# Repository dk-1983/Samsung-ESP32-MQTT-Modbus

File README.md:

# Samsung-ESP32-MQTT-Modbus — 1.0.2

[Русский](README_RU.md)

**[Download stable v1.0.2](https://github.com/dk-1983/Samsung-ESP32-MQTT-Modbus/releases/tag/v1.0.2)** — ready-made OTA binary for already provisioned ESP32-S3 N16R8 controllers. Not a first-install image for a blank board.

**Keep Samsung's factory features and add 4VRS control.**

Samsung-ESP32-MQTT-Modbus is an ESP32-S3 expansion controller with a transparent
inline UART bridge between the AC motherboard and its original display/Wi-Fi board.
The architecture is designed to preserve the full factory functionality: the
original boards keep communicating, while the IR remote, display and Samsung
SmartThings coexist with the additional 4VRS interfaces.

Our 4VRS polling and command dispatcher runs on the ESP32. It tracks factory
transactions, selects an idle window for each own request and coordinates access
from the web controls, MQTT and Modbus to the shared UART bus. A command is confirmed
only by reading the actual AC state. Unknown factory packets are forwarded unchanged,
so forwarding is not limited to the commands implemented by our firmware.

Additional interfaces:

- **Wi-Fi:** local network connectivity and OTA firmware updates.
- **HTTP Remote:** a local web remote and HTTP API for control over the network.
- **MQTT / Home Assistant Discovery:** automatic device and entity discovery. No custom Samsung/4VRS integration, HACS package or manual entity configuration is required; use the standard MQTT integration with your broker.
- **Modbus RTU / TCP:** RS485 and network automation integration.

Local 4VRS interfaces do not require Samsung's cloud. Factory SmartThings retains
its own connection through the original Wi-Fi module. Display, IR remote and
SmartThings control have been checked with the bridge on AR24BSFCMWKNER;
exhaustive validation of every factory function is still pending.

Repository: [dk-1983/Samsung-ESP32-MQTT-Modbus](https://github.com/dk-1983/Samsung-ESP32-MQTT-Modbus).
See [bridge wiring and limitations](docs/UART_BRIDGE.md).

Home Assistant is optional: connect the controller to your own MQTT broker and automation server. See [topics, commands, states and the complete Discovery-based inventory](docs/HOME_ASSISTANT.md#own-mqtt-broker-without-home-assistant).

[Complete Modbus register list with Samsung / 4VRS separation](docs/MODBUS.md): the factory indoor-unit range ends at **2449**, and our extensions begin at **2450**.

[Electrical schematic, wiring and PCB component libraries](hardware/README.md).

## Home Assistant via Modbus Devices

**[Modbus Devices](https://github.com/dk-1983/Modbus_Devices#4vrs) includes a dedicated profile for this controller: manufacturer `4VRS`, model `Samsung-ESP32-Modbus`.**

Connect through Modbus TCP over Wi-Fi or Modbus RTU over RS485 to get climate
control, the full fan/swing/preset controls, confirmed writes, and link and command
diagnostics in Home Assistant. The profile uses our extended register map;
you do not need to enter each register manually. MQTT is not required for this option.

1. Install [Modbus Devices](https://github.com/dk-1983/Modbus_Devices#installation) in Home Assistant.
2. Open `/modbus` on the controller and enable TCP or RTU.
3. Add the device using **4VRS → Samsung-ESP32-Modbus** and your connection settings.
   For direct TCP, use the controller IP, port **502** and configured Unit ID (default **1**).
   For RTU, match the controller's serial settings (default **9600 8E1**).

Select the **4VRS** profile for this device; the Samsung **MIM-B19N(T)** profile
is for the factory adapter. For MQTT-based setup, use Home Assistant's standard
MQTT integration with Discovery as described above.

## Electrical schematic

Motherboard UART: **RX18 / TX17**. Original display/Wi-Fi board: **RX15 / TX16**.
Modbus RS485: **RX8 / TX9 / DE21**. Numbers are ESP32 GPIOs, not module pad numbers.
Both Samsung boards retain their +5 V and common ground connections.

[Open full-resolution schematic](hardware/drawings/preview-1.png) · [Vector PDF](hardware/drawings/Samsung_transparency_bridge_revA-review.pdf) · [PCB component libraries](hardware/README.md)

## Controls and connections

The portal on port 80 links to controls, MQTT, Modbus and GitHub updates.
The Control link opens `/control`; advanced ESPHome controls remain on port 8080.
Both use `admin` and the same password stored on the device.

The main web interface on port 80 supports English and Russian. English is the
default; use the language selector to switch. Your browser remembers the selection.
This selector does not change the advanced ESPHome interface on port 8080.

- Independent persistent checkboxes for MQTT, Modbus RTU and Modbus TCP; all default off.
- Browser-configured MQTT broker/port/credentials/topic prefix and Home Assistant discovery.
- Browser-configured Modbus unit and RS485 baud rate; RTU defaults to 9600 8E1, TCP port 502.
- GitHub automatic-install checkbox, manual check/install, progress, signed manifest,
  board profile, SHA256 validation and rollback.
- Local ESPHome OTA remains available and is coordinated with the GitHub worker.

[Management and releases](docs/MANAGEMENT.md) · [Full device register map](docs/MODBUS.md)
· [Home Assistant MQTT Discovery](docs/HOME_ASSISTANT.md)
· [Modbus register reference (Russian)](docs/MODBUS_REGISTERS_RU.md)
· [UART function reference](docs/FUNCTIONS_RU.md)

UART TX/RX GPIO17/18 uses 9600 8N1. RS485 TX/RX/DE uses 9/8/21.
The AC uses D0 UART, not native Modbus; ESP32 implements the external register map.
Core addresses follow MIM-B19N/B19NT; custom functions begin at 2450.

UART is enabled on every boot and can be disabled in the control page.
Saving MQTT settings reboots the controller after two seconds to apply credentials.
Feedback is never optimistic: acknowledgement is not proof of the requested AC state.

## Hardware compatibility, first installation and updates

**Inline bridge support starts with firmware 0.5.0. Versions 0.4.x use the earlier
non-bridge configuration; 0.5.0 and later target the bridge wiring shown here.**
From the ESP32 side, the AC motherboard uses RX GPIO18 / TX GPIO17, the original
Wi-Fi/display board uses RX GPIO15 / TX GPIO16, and Modbus RS485 uses
RX GPIO8 / TX GPIO9 / DE GPIO21.
Module pads 8/9 are GPIO15/16 (the bridge), not GPIO8/9 (Modbus).

Boards wired for the pre-0.5.0 non-bridge configuration are a different hardware
configuration.
Do not install the current OTA on them solely because their firmware version is
older. Check the wiring against the current schematic first; an OTA update does
not add the missing bridge connection or change the PCB routing.

- **Configured controller with the current bridge wiring:** update through
  `/updates`. A working 1.0.0 or 1.0.1 installation on this hardware can update
  directly; no intermediate version is required. Preserve NVS when updating.
- **New controller with the current bridge wiring:** build the current stable
  source with `./Build.ps1`, personal `secrets.yaml` and `public_release: "false"`
  (the default). Use `firmware.factory.bin` for initial USB/serial installation.
  First boot saves the web, local OTA and Samsung-Setup passwords in NVS.
  Connect to Samsung-Setup with your setup password and configure Wi-Fi at
  `http://192.168.4.1:8080/`. Subsequent updates can use public OTA releases.

The public `*-ota.bin` requires existing device credentials in NVS; it is not a
first-install image for a blank board. A ready-made public provisioning image is
not provided yet. Installing an old firmware version first is not required.
Hardware compatibility and initial credential provisioning are separate requirements.

## Build and validation

Run `./Build.ps1` to install pinned dependencies, run host tests and build, without
flashing. Local configuration is in `secrets.yaml`; neither it nor locally built
private binaries belong in a public release. OTA/factory binaries are under
`work/build/.pioenvs/samsung-s3`. On the first local build boot, credentials are saved
to NVS and survive subsequent public OTA updates.

The separate GitHub workflow prepares a clean public **OTA-only** artifact for
controllers with the current bridge wiring and provisioned credentials. Signing/publishing is a separate step.
See [release preparation](docs/MANAGEMENT.md#release).

Power, fan Low/Medium/High/Turbo and both swing axes were tested on the target AC
in earlier firmware. Persistent web settings, Modbus TCP and GitHub OTA have
been checked on a device, including credential/settings retention and boot confirmation.
Authenticated MQTT connectivity is verified. Physical RS485 and forced rollback still need testing.
Experimental legacy controls require per-function verification on this model.

[Protocol](docs/PROTOCOL.md) · [Attribution](THIRD_PARTY.md)

The `/about` page shows firmware, memory, connections and UART freshness.
Restart requires confirmation and preserves settings. It is rejected during OTA
or while an AC command is pending.

`/settings` independently changes web, local OTA and Samsung-Setup passwords.
Blank fields preserve current credentials; new values require confirmation.
Changes are stored in NVS and applied on restart. Forgotten-password recovery
is not implemented yet.

`/wifi` shows network, IP, MAC, signal and channel. `/wifi/reset` confirms a
Wi-Fi-only reset; reprovision through Samsung-Setup at `192.168.4.1:8080`.
Other settings are preserved.

[Overview, web controls and MQTT power commands (Russian)](docs/CONTROL_RU.md).

HVAC commands require fresh control permission and feedback. Requested power is
never restored automatically after a restart.

In inline mode the factory board owns startup and notification ACKs. Own writes
require fresh permission and feedback, use an idle transaction window and are
confirmed by own readback, never by ACK alone. No automatic write retries.
Main RX18/TX17, factory RX15/TX16, RS485 RX8/TX9/DE21. All three hardware
UARTs are used; serial logging is disabled, web logging remains available.
Disabling UART transmission also stops factory forwarding.

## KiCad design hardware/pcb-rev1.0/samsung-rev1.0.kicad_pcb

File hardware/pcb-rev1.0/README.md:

# Samsung UART bridge — PCB rev1.0

[Русский](README_RU.md)

30 × 48 mm (48 × 30 when rotated), two copper layers, 1.0 mm thickness in KiCad. Components on both sides, no mounting holes. Based on the Haier pcb-v1.1 circuit; the Haier project was not modified.

Files: samsung-rev1.0.kicad_pcb; review/samsung-both-sides.png (review only); circuit.json, connections.csv and BOM.csv; drc.json; review/pin-check.json; reproducible scripts in sources/.

KiCad DRC: 0 violations and 0 unconnected items. All 82 assigned logical pads match circuit.json. 25 U1/U2/U3 assignments independently match the Samsung schematic. This PCB has not been tested on hardware. Gerber and drill files are included in production/, together with an archive and a checksum manifest.

## Solder pads

MAIN and DISPLAY TX/RX labels refer to the external Samsung board, not the ESP.

- TP9–TP12 MAIN, left to right viewed from top: +5V, GND, motherboard TX through divider to GPIO18, motherboard RX from GPIO17.
- TP13–TP16 DISPLAY: +5V, GND, display TX through divider to GPIO15, display RX from GPIO16.
- TP7/TP8: RS485 A/B.
- TP1/TP2/TP3: programming TX0 GPIO43 / RX0 GPIO44 / GND.
- TP4/TP5/TP6 on bottom: EN / BOOT GPIO0 / 3V3 voltage monitor.

UART solder pads are 2 mm in diameter. No UART connectors. All power and grounds are common. Preserve factory Samsung connections outside the UART bridge.

RS485 uses GPIO8 RX, GPIO9 TX, GPIO21 DE and /RE. R6 10k pulls direction down. R7 120 ohm and solder jumper JP1 enable termination. All three RX inputs use 10k/20k dividers; ESP TX outputs are direct 3.3V.

## Assembly and references

PCB component numbering follows the Haier carrier and differs from the older Samsung revA PDF. Use this PCB's BOM.csv and connections.csv. Old Samsung resistor → PCB mapping: R1→R1, R2→R9, R3→R8, R4→R2, R5→R3, R6→R5, R7→R4, R8→R6. PCB R7 adds termination.

The Haier power circuit is retained: LM1117-3.3 SOT-223, 220uF and 100uF case-C capacitors and ceramic decoupling. This expands the old Samsung revA drawing, whose 47uF C2 package was unresolved. The regulator TAB and its thermal planes are +3V3, not GND. ESP ground planes and thermal vias remain separate. Both copper layers are clear beneath the antenna.

This PCB requires factory plated holes, unlike the homemade kitchen-hood PCB. Verify mechanical fit and the BOM against available components before ordering. No firmware, device or release changes were performed.

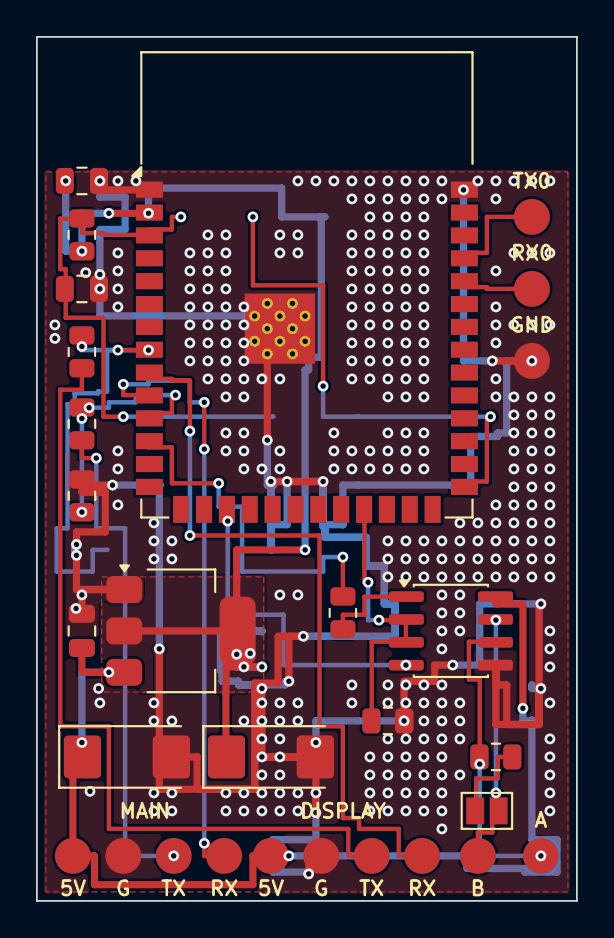
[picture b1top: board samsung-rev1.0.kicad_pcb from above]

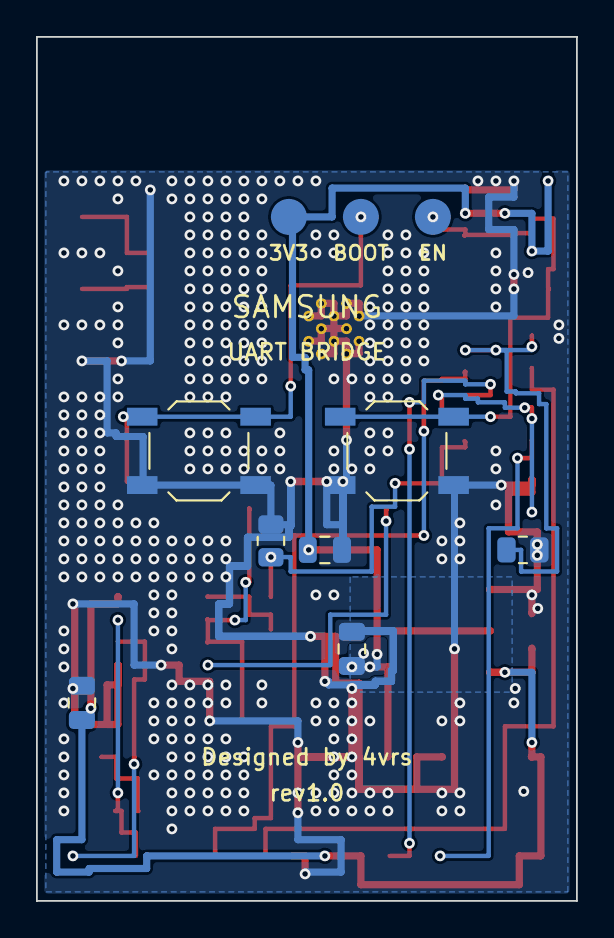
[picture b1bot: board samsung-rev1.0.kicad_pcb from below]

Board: 2 copper layers, 30.0 x 48.0 mm, 39 parts (10 on the bottom side), 20 nets.

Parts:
C1: 220u 10V; CP_EIA-6032-28_Kemet-C
C2, C4, C5, C6: 100n 50V; C_0805_2012Metric
C3: 100u 10V; CP_EIA-6032-28_Kemet-C
C7: 1u 16V; C_0805_2012Metric
C8: 10u 10V; C_0805_2012Metric
JP1: TERM ENABLE; SolderJumper-2_P1.3mm_Open_Pad1.0x1.5mm
R1, R2, R4, R6, R8: 10k; R_0805_2012Metric
R3, R5, R9: 20k; R_0805_2012Metric
R7: 120; R_0805_2012Metric
SB1: SB1; SW_SPST_TL3342
SB2: SB2; SW_SPST_TL3342
TP1: UART0_TX; TestPoint_Pad_D2.0mm
TP2: UART0_RX; TestPoint_Pad_D2.0mm
TP3, TP10, TP14: GND; TestPoint_Pad_D2.0mm
TP4: EN; TestPoint_Pad_D2.0mm
TP5: BOOT; TestPoint_Pad_D2.0mm
TP6: +3V3; TestPoint_Pad_D2.0mm
TP7: A; TestPoint_Pad_D2.0mm
TP8: B; TestPoint_Pad_D2.0mm
TP9, TP13: +5V; TestPoint_Pad_D2.0mm
TP11: MAIN_TX_5V; TestPoint_Pad_D2.0mm
TP12: H_TX; TestPoint_Pad_D2.0mm
TP15: FACTORY_TX; TestPoint_Pad_D2.0mm
TP16: F_TX; TestPoint_Pad_D2.0mm
U1: ESP32-S3-WROOM-1-N16R8; ESP32-S3-WROOM-1
U2: LM1117-3.3; SOT-223-3_TabPin2
U3: MAX485; SOIC-8_3.9x4.9mm_P1.27mm

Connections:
+3V3: C3.1, C4.1, C5.1, C8.1, R1.1, TP6.1, U1.2, U2.2
+5V: C1.1, C2.1, C6.1, TP9.1, TP13.1, U2.3, U3.8
A: R7.1, TP7.1, U3.6
B: JP1.2, TP8.1, U3.7
BOOT: SB1.1, TP5.1, U1.27
DIR: R6.1, U1.23, U3.2, U3.3
EN: C7.1, R1.2, SB2.1, TP4.1, U1.3
FACTORY_TX: R8.1, TP15.1
F_RX: R8.2, R9.1, U1.8
F_TX: TP16.1, U1.9
GND: C1.2, C2.2, C3.2, C4.2, C5.2, C6.2, C7.2, C8.2, R3.2, R5.2, R6.2, R9.2, SB1.2, SB2.2, TP3.1, TP10.1, TP14.1, U1.1, U1.40, U1.41, U2.1, U3.5
H_RX: R2.2, R3.1, U1.11
H_TX: TP12.1, U1.10
MAIN_TX_5V: R2.1, TP11.1
MB_RX: R4.2, R5.1, U1.12
MB_TX: U1.17, U3.4
RO_5V: R4.1, U3.1
TERM: JP1.1, R7.2
UART0_RX: TP2.1, U1.36
UART0_TX: TP1.1, U1.37

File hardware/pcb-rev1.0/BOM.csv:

Reference,Value,Footprint,MPN
U1,ESP32-S3-WROOM-1-N16R8,RF_Module:ESP32-S3-WROOM-1,ESP32-S3-WROOM-1-N16R8
U2,LM1117-3.3,Package_TO_SOT_SMD:SOT-223-3_TabPin2,LM1117MP-3.3
U3,MAX485,Package_SO:SOIC-8_3.9x4.9mm_P1.27mm,MAX485ESA+
R1,10k,Resistor_SMD:R_0805_2012Metric,
R2,10k,Resistor_SMD:R_0805_2012Metric,
R3,20k,Resistor_SMD:R_0805_2012Metric,
R4,10k,Resistor_SMD:R_0805_2012Metric,
R5,20k,Resistor_SMD:R_0805_2012Metric,
R8,10k,Resistor_SMD:R_0805_2012Metric,
R9,20k,Resistor_SMD:R_0805_2012Metric,
R6,10k,Resistor_SMD:R_0805_2012Metric,
R7,120,Resistor_SMD:R_0805_2012Metric,
C1,220u 10V,Capacitor_Tantalum_SMD:CP_EIA-6032-28_Kemet-C,TAJC227M010RNJ
C3,100u 10V,Capacitor_Tantalum_SMD:CP_EIA-6032-28_Kemet-C,TAJC107M010RNJ
C2,100n 50V,Capacitor_SMD:C_0805_2012Metric,
C4,100n 50V,Capacitor_SMD:C_0805_2012Metric,
C5,100n 50V,Capacitor_SMD:C_0805_2012Metric,
C6,100n 50V,Capacitor_SMD:C_0805_2012Metric,
C7,1u 16V,Capacitor_SMD:C_0805_2012Metric,
C8,10u 10V,Capacitor_SMD:C_0805_2012Metric,
SB1,SB1,Button_Switch_SMD:SW_SPST_TL3342,
SB2,SB2,Button_Switch_SMD:SW_SPST_TL3342,
JP1,TERM ENABLE,Jumper:SolderJumper-2_P1.3mm_Open_Pad1.0x1.5mm,
TP1,UART0_TX,TestPoint:TestPoint_Pad_D2.0mm,
TP2,UART0_RX,TestPoint:TestPoint_Pad_D2.0mm,
TP3,GND,TestPoint:TestPoint_Pad_D2.0mm,
TP4,EN,TestPoint:TestPoint_Pad_D2.0mm,
TP5,BOOT,TestPoint:TestPoint_Pad_D2.0mm,
TP6,+3V3,TestPoint:TestPoint_Pad_D2.0mm,
TP7,A,TestPoint:TestPoint_Pad_D2.0mm,
TP8,B,TestPoint:TestPoint_Pad_D2.0mm,
TP9,+5V,TestPoint:TestPoint_Pad_D2.0mm,
TP10,GND,TestPoint:TestPoint_Pad_D2.0mm,
TP11,MAIN_TX_5V,TestPoint:TestPoint_Pad_D2.0mm,
TP12,H_TX,TestPoint:TestPoint_Pad_D2.0mm,
TP13,+5V,TestPoint:TestPoint_Pad_D2.0mm,
TP14,GND,TestPoint:TestPoint_Pad_D2.0mm,
TP15,FACTORY_TX,TestPoint:TestPoint_Pad_D2.0mm,
TP16,F_TX,TestPoint:TestPoint_Pad_D2.0mm,
